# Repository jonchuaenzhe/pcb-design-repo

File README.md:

2020 May - Present
# PCB Design Archives

This repository is an archive of past completed PCB Designs on EAGLE and Altium for various projects.

## Altium

For the Altium Projects, the Schematics can be viewed by accessing the "Project Outputs" folder within each project and opening the schematic PDF file.

## EAGLE

For the EAGLE Projects, the Schematics and Layouts can be viewed directly in each project folder as a PDF file.

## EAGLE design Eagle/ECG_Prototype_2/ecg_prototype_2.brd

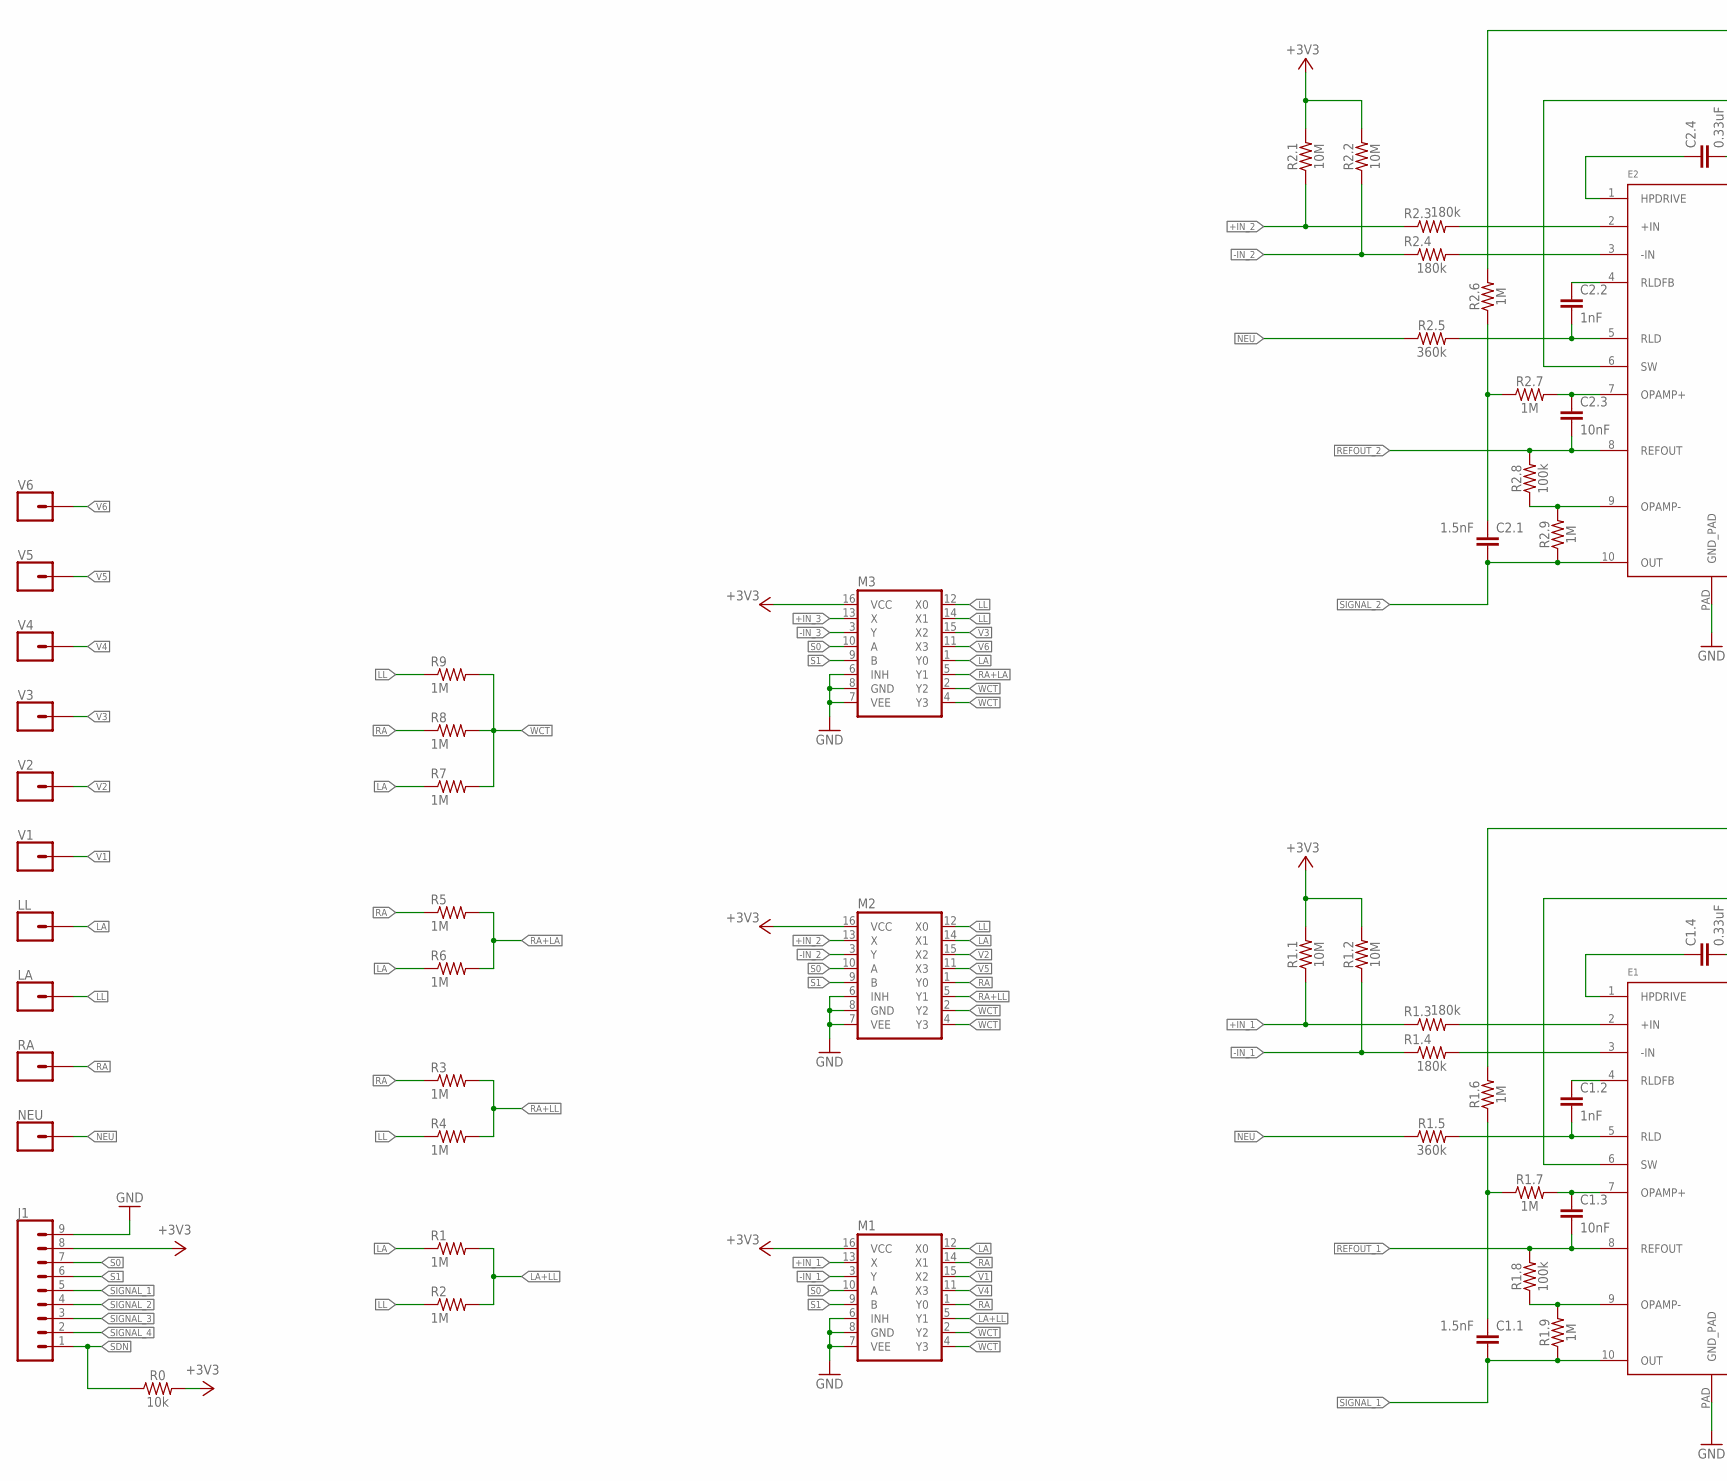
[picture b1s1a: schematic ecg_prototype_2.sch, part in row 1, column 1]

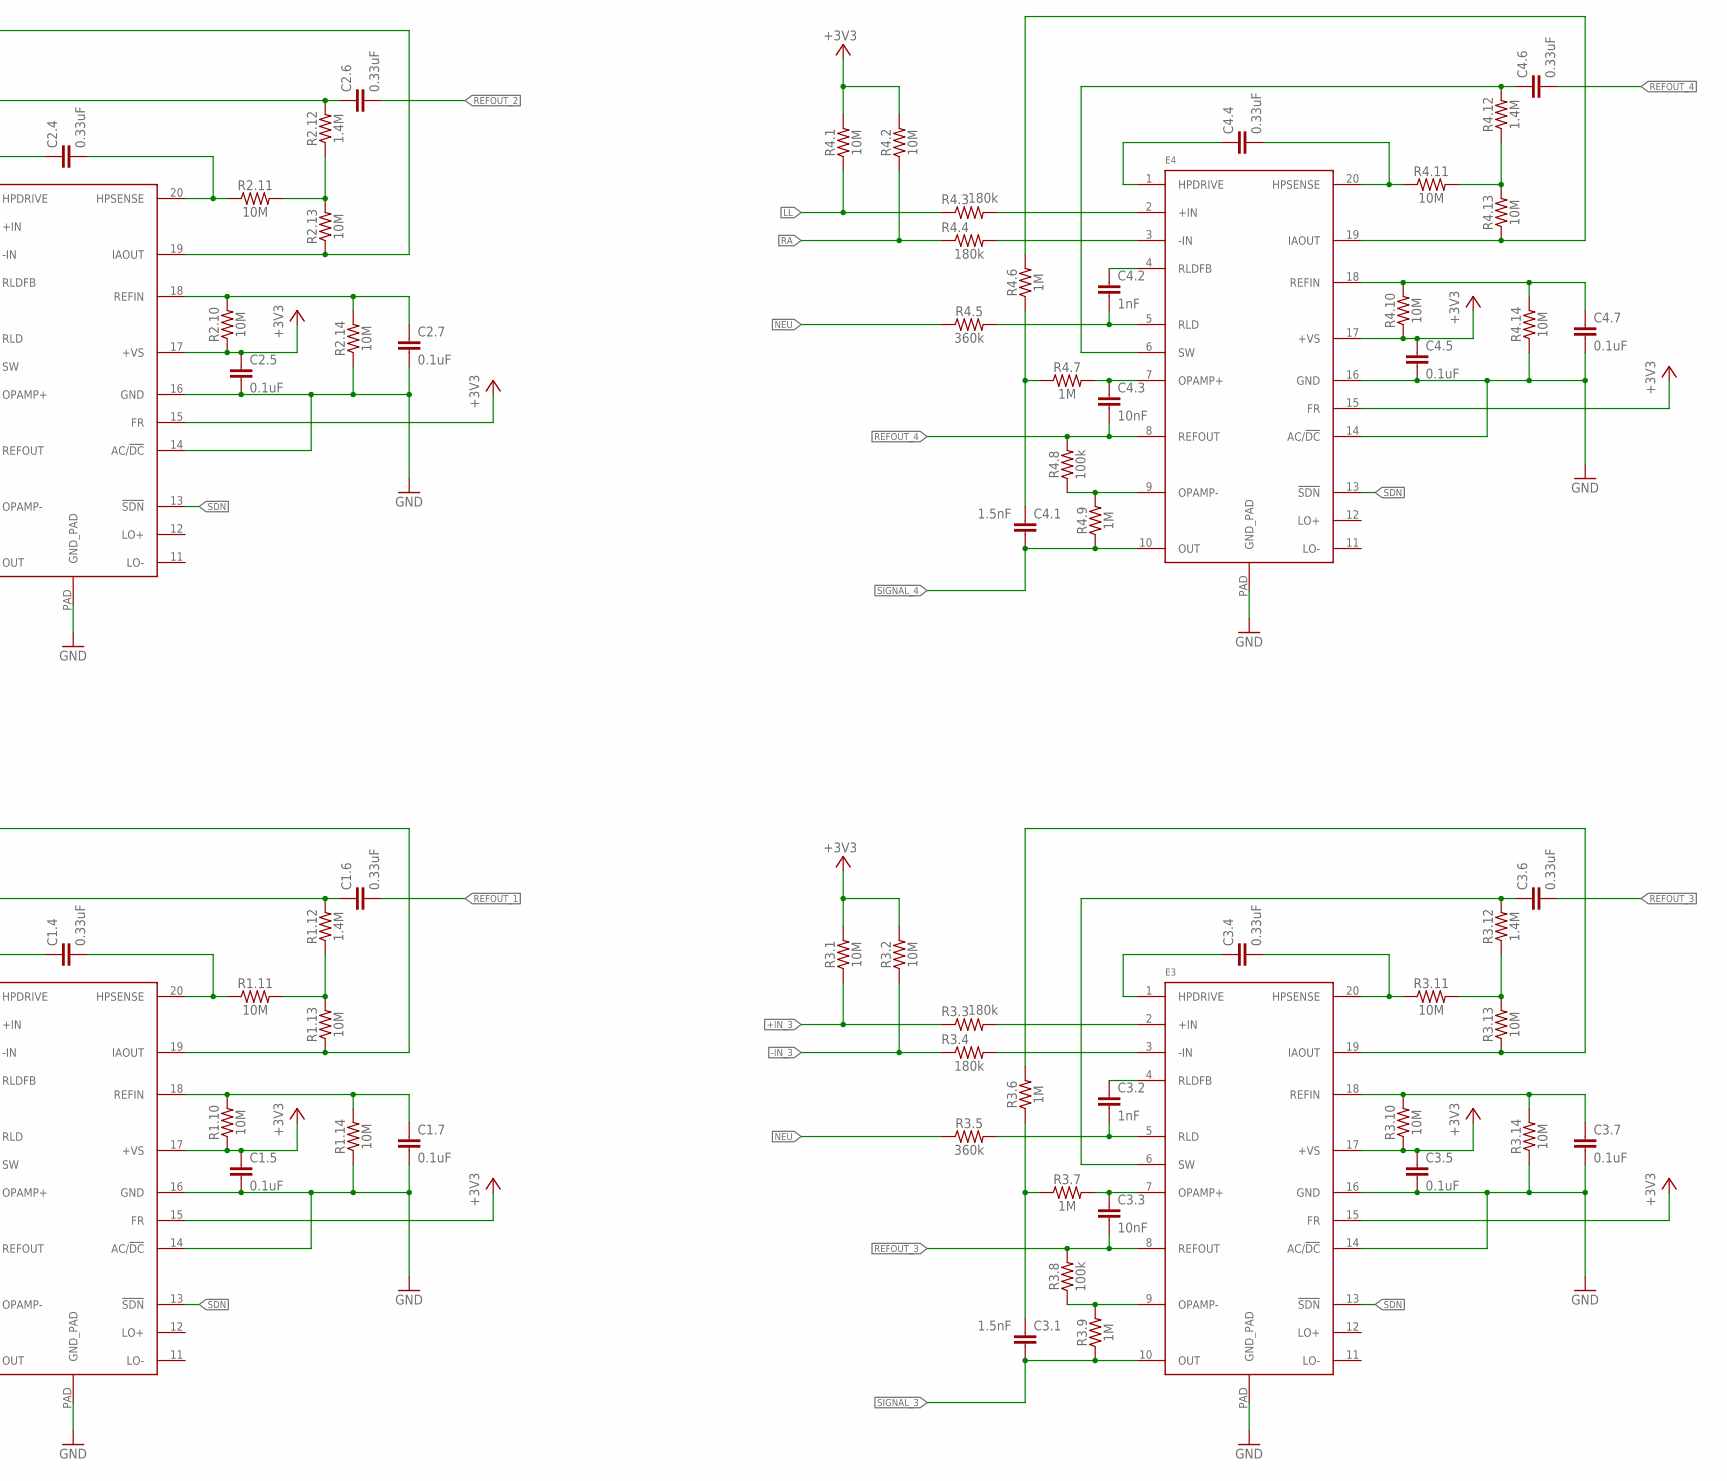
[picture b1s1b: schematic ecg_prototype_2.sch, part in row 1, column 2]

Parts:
C1.1, C2.1, C3.1, C4.1: 1.5nF; 0603-CAP
C1.2, C2.2, C3.2, C4.2: 1nF; 0603-CAP
C1.3, C2.3, C3.3, C4.3: 10nF; 0603-CAP
C1.4, C1.6, C2.4, C2.6, C3.4, C3.6, C4.4, C4.6: 0.33uF; 0805
C1.5, C1.7, C2.5, C2.7, C3.5, C3.7, C4.5, C4.7: 0.1uF; 0603-CAP
E1, E2, E3, E4: AD8232ACPZ-R7; LFCSP_20
J1: CONN_09; 1X09
LA: CONN_01; 1X01
LL: CONN_01; 1X01
M1, M2, M3: 74HC4052D; SO16
NEU: CONN_01; 1X01
R0: 10k; 0603
R1, R2, R3, R4, R5, R6, R7, R8, R9: 1M; 0402-RES
R1.1, R1.2, R1.10, R1.11, R1.13, R1.14, R2.1, R2.2, R2.10, R2.11, R2.13, R2.14, R3.1, R3.2, R3.10, R3.11, R3.13, R3.14, R4.1, R4.2, R4.10, R4.11, R4.13, R4.14: 10M; 0603
R1.3, R1.4, R2.3, R2.4, R3.3, R3.4, R4.3, R4.4: 180k; 0603
R1.5, R2.5, R3.5, R4.5: 360k; 0603
R1.6, R1.7, R1.9, R2.6, R2.7, R2.9, R3.6, R3.7, R3.9, R4.6, R4.7, R4.9: 1M; 0603
R1.8, R2.8, R3.8, R4.8: 100k; 0603
R1.12, R2.12, R3.12, R4.12: 1.4M; 0603
RA: CONN_01; 1X01
V1, V2, V3, V4, V5, V6: CONN_01; 1X01

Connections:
+3V3: C1.5.1, C2.5.1, C3.5.1, C4.5.1, E1.15 (FR), E1.17 (+VS), E2.15 (FR), E2.17 (+VS), E3.15 (FR), E3.17 (+VS), E4.15 (FR), E4.17 (+VS), J1.8, M1.16 (VCC), M2.16 (VCC), M3.16 (VCC), R0.2, R1.1.2, R1.2.2, R1.10.1, R2.1.2, R2.2.2, R2.10.1, R3.1.2, R3.2.2, R3.10.1, R4.1.2, R4.2.2, R4.10.1
+IN_1: M1.13 (X), R1.1.1, R1.3.1
+IN_2: M2.13 (X), R2.1.1, R2.3.1
+IN_3: M3.13 (X), R3.1.1, R3.3.1
-IN_1: M1.3 (Y), R1.2.1, R1.4.1
-IN_2: M2.3 (Y), R2.2.1, R2.4.1
-IN_3: M3.3 (Y), R3.2.1, R3.4.1
GND: C1.5.2, C1.7.2, C2.5.2, C2.7.2, C3.5.2, C3.7.2, C4.5.2, C4.7.2, E1.14 (AC/!DC), E1.16 (GND), E1.PAD (GND_PAD), E2.14 (AC/!DC), E2.16 (GND), E2.PAD (GND_PAD), E3.14 (AC/!DC), E3.16 (GND), E3.PAD (GND_PAD), E4.14 (AC/!DC), E4.16 (GND), E4.PAD (GND_PAD), J1.9, M1.6 (INH), M1.7 (VEE), M1.8 (GND), M2.6 (INH), M2.7 (VEE), M2.8 (GND), M3.6 (INH), M3.7 (VEE), M3.8 (GND), R1.14.1, R2.14.1, R3.14.1, R4.14.1
LA: LL.1, M1.12 (X0), M2.14 (X1), M3.1 (Y0), R1.1, R6.1, R7.1
LA+LL: M1.5 (Y1), R1.2, R2.2
LL: LA.1, M2.12 (X0), M3.12 (X0), M3.14 (X1), R2.1, R4.1, R4.1.1, R4.3.1, R9.1
unnamed: E1.9 (OPAMP-), R1.8.1, R1.9.2
unnamed: E2.2 (+IN), R2.3.2
unnamed: E1.2 (+IN), R1.3.2
unnamed: E1.3 (-IN), R1.4.2
unnamed: E2.3 (-IN), R2.4.2
unnamed: C1.1.1, R1.6.1, R1.7.1
unnamed: C1.3.1, E1.7 (OPAMP+), R1.7.2
unnamed: C1.2.1, E1.4 (RLDFB)
unnamed: C1.2.2, E1.5 (RLD), R1.5.2
unnamed: E1.19 (IAOUT), R1.6.2, R1.13.1
unnamed: C1.6.1, E1.6 (SW), R1.12.2
unnamed: C1.7.1, E1.18 (REFIN), R1.10.2, R1.14.2
unnamed: R1.11.2, R1.12.1, R1.13.2
unnamed: C1.4.2, E1.20 (HPSENSE), R1.11.1
unnamed: C1.4.1, E1.1 (HPDRIVE)
unnamed: C2.2.1, E2.4 (RLDFB)
unnamed: C2.2.2, E2.5 (RLD), R2.5.2
unnamed: C2.1.1, R2.6.1, R2.7.1
unnamed: C2.3.1, E2.7 (OPAMP+), R2.7.2
unnamed: E2.9 (OPAMP-), R2.8.1, R2.9.2
unnamed: E2.19 (IAOUT), R2.6.2, R2.13.1
unnamed: C2.6.1, E2.6 (SW), R2.12.2
unnamed: R2.11.2, R2.12.1, R2.13.2
unnamed: C2.4.2, E2.20 (HPSENSE), R2.11.1
unnamed: C2.4.1, E2.1 (HPDRIVE)
unnamed: C2.7.1, E2.18 (REFIN), R2.10.2, R2.14.2
unnamed: E3.2 (+IN), R3.3.2
unnamed: E3.3 (-IN), R3.4.2
unnamed: C3.2.1, E3.4 (RLDFB)
unnamed: C3.2.2, E3.5 (RLD), R3.5.2
unnamed: C3.1.1, R3.6.1, R3.7.1
unnamed: C3.3.1, E3.7 (OPAMP+), R3.7.2
unnamed: E3.9 (OPAMP-), R3.8.1, R3.9.2
unnamed: E3.19 (IAOUT), R3.6.2, R3.13.1
unnamed: C3.6.1, E3.6 (SW), R3.12.2
unnamed: R3.11.2, R3.12.1, R3.13.2
unnamed: C3.4.2, E3.20 (HPSENSE), R3.11.1
unnamed: C3.4.1, E3.1 (HPDRIVE)
unnamed: C3.7.1, E3.18 (REFIN), R3.10.2, R3.14.2
unnamed: E4.2 (+IN), R4.3.2
unnamed: E4.3 (-IN), R4.4.2
unnamed: C4.2.1, E4.4 (RLDFB)
unnamed: C4.2.2, E4.5 (RLD), R4.5.2
unnamed: C4.1.1, R4.6.1, R4.7.1
unnamed: C4.3.1, E4.7 (OPAMP+), R4.7.2
unnamed: E4.9 (OPAMP-), R4.8.1, R4.9.2
unnamed: E4.19 (IAOUT), R4.6.2, R4.13.1
unnamed: C4.6.1, E4.6 (SW), R4.12.2
unnamed: R4.11.2, R4.12.1, R4.13.2
unnamed: C4.4.2, E4.20 (HPSENSE), R4.11.1
unnamed: C4.4.1, E4.1 (HPDRIVE)
unnamed: C4.7.1, E4.18 (REFIN), R4.10.2, R4.14.2
NEU: NEU.1, R1.5.1, R2.5.1, R3.5.1, R4.5.1
RA: M1.1 (Y0), M1.14 (X1), M2.1 (Y0), R3.1, R4.2.1, R4.4.1, R5.1, R8.1, RA.1
RA+LA: M3.5 (Y1), R5.2, R6.2
RA+LL: M2.5 (Y1), R3.2, R4.2
REFOUT_1: C1.3.2, C1.6.2, E1.8 (REFOUT), R1.8.2
REFOUT_2: C2.3.2, C2.6.2, E2.8 (REFOUT), R2.8.2
REFOUT_3: C3.3.2, C3.6.2, E3.8 (REFOUT), R3.8.2
REFOUT_4: C4.3.2, C4.6.2, E4.8 (REFOUT), R4.8.2
S0: J1.7, M1.10 (A), M2.10 (A), M3.10 (A)
S1: J1.6, M1.9 (B), M2.9 (B), M3.9 (B)
SDN: E1.13 (!SDN), E2.13 (!SDN), E3.13 (!SDN), E4.13 (!SDN), J1.1, R0.1
SIGNAL_1: C1.1.2, E1.10 (OUT), J1.5, R1.9.1
SIGNAL_2: C2.1.2, E2.10 (OUT), J1.4, R2.9.1
SIGNAL_3: C3.1.2, E3.10 (OUT), J1.3, R3.9.1
SIGNAL_4: C4.1.2, E4.10 (OUT), J1.2, R4.9.1
V1: M1.15 (X2), V1.1
V2: M2.15 (X2), V2.1
V3: M3.15 (X2), V3.1
V4: M1.11 (X3), V4.1
V5: M2.11 (X3), V5.1
V6: M3.11 (X3), V6.1
WCT: M1.2 (Y2), M1.4 (Y3), M2.2 (Y2), M2.4 (Y3), M3.2 (Y2), M3.4 (Y3), R7.2, R8.2, R9.2

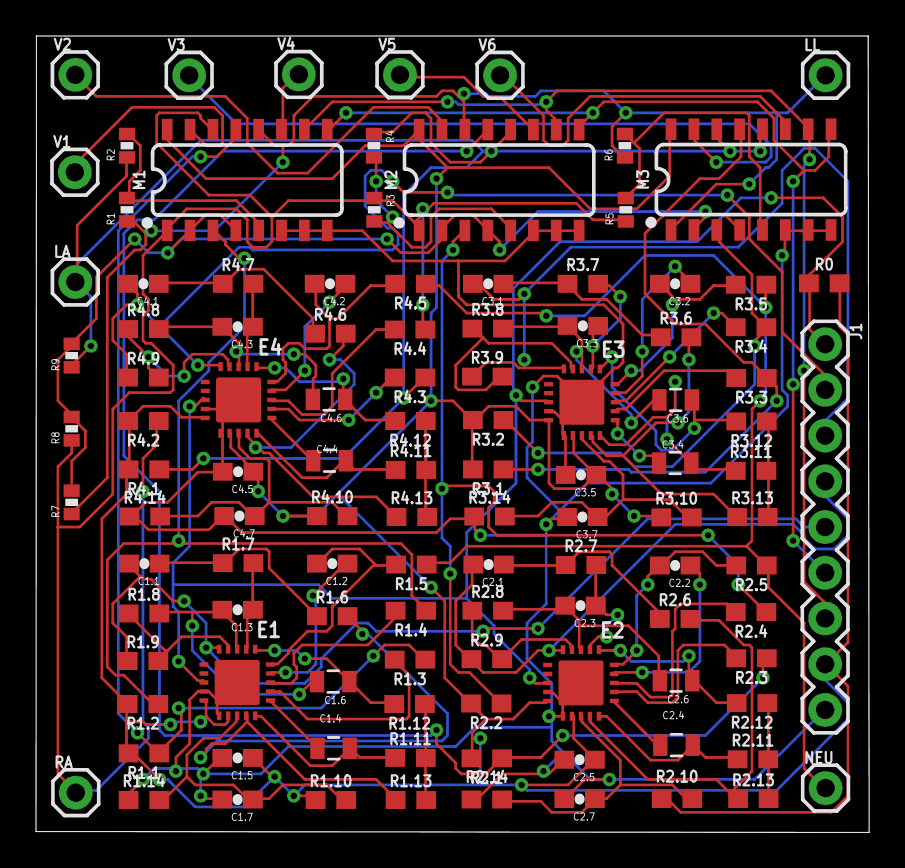
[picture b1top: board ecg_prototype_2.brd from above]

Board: 2 copper layers, 46.3 x 44.2 mm, 112 parts (0 on the bottom side), 85 nets.

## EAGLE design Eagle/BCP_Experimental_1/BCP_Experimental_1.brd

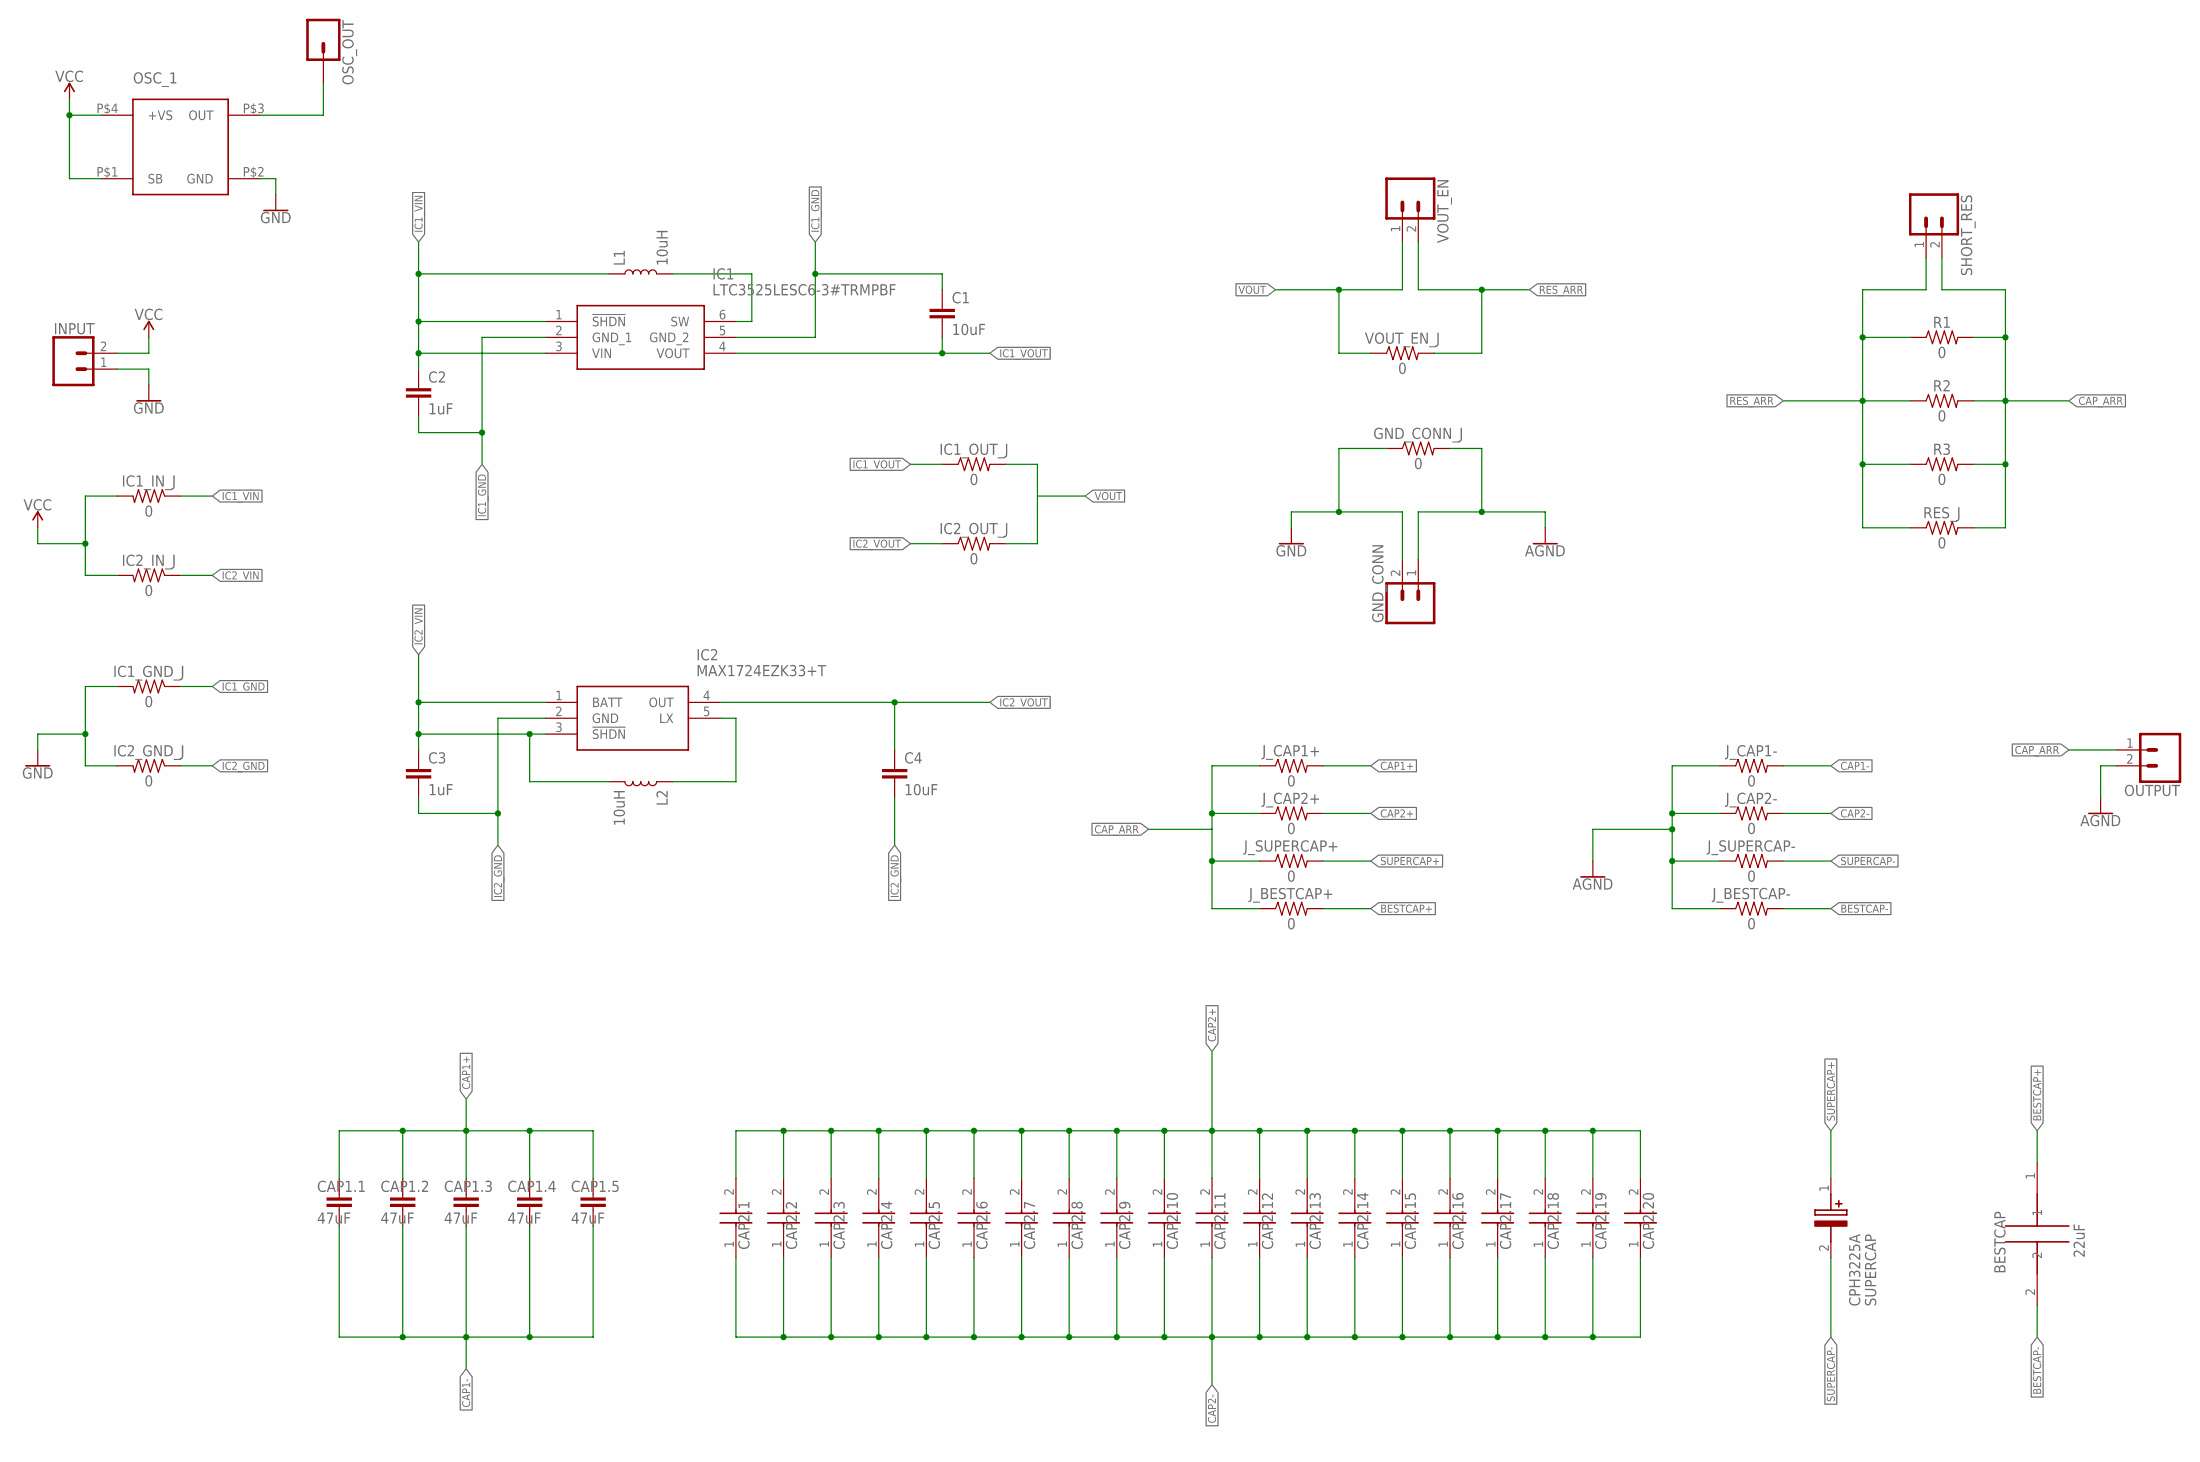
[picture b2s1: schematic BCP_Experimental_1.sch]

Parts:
BESTCAP: BZ054B223ZNB
C1, C4: 10uF; 0603
C2, C3: 1uF; 0603
CAP1.1, CAP1.2, CAP1.3, CAP1.4, CAP1.5: 47uF; 1206
CAP2.1, CAP2.2, CAP2.3, CAP2.4, CAP2.5, CAP2.6, CAP2.7, CAP2.8, CAP2.9, CAP2.10, CAP2.11, CAP2.12, CAP2.13, CAP2.14, CAP2.15, CAP2.16, CAP2.17, CAP2.18, CAP2.19, CAP2.20: AMK432BJ477MM-T; CAPC4532X270N
GND_CONN: CONN_02; 1X02
GND_CONN_J: 0; 0402
IC1: LTC3525LESC6-3#TRMPBF; SOT65P210X100-6N
IC1_GND_J, IC1_IN_J, IC1_OUT_J, IC2_GND_J, IC2_IN_J, IC2_OUT_J: 0; 0402
IC2: MAX1724EZK33+T; SOT95P275X110-5N
INPUT: CONN_02; 1X02
J_BESTCAP+: 0; 0402
J_BESTCAP-: 0; 0402
J_CAP1+, J_CAP1-, J_CAP2+, J_CAP2-: 0; 0402
J_SUPERCAP+: 0; 0402
J_SUPERCAP-: 0; 0402
L1, L2: 10uH; 0603
OSC_1: 830202536501
OSC_OUT: CONN_01; 1X01
OUTPUT: CONN_02; 1X02
R1, R2, R3: 0; 0603
RES_J: 0; 0402
SHORT_RES: CONN_02; 1X02
SUPERCAP: CPH3225A
VOUT_EN: CONN_02; 1X02
VOUT_EN_J: 0; 0402

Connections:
AGND: GND_CONN.1, GND_CONN_J.2, J_BESTCAP-.1, J_CAP1-.1, J_CAP2-.1, J_SUPERCAP-.1, OUTPUT.2
BESTCAP+: BESTCAP.1, J_BESTCAP+.2
BESTCAP-: BESTCAP.2, J_BESTCAP-.2
CAP1+: CAP1.1.1, CAP1.2.1, CAP1.3.1, CAP1.4.1, CAP1.5.1, J_CAP1+.2
CAP1-: CAP1.1.2, CAP1.2.2, CAP1.3.2, CAP1.4.2, CAP1.5.2, J_CAP1-.2
CAP2+: CAP2.1.2, CAP2.2.2, CAP2.3.2, CAP2.4.2, CAP2.5.2, CAP2.6.2, CAP2.7.2, CAP2.8.2, CAP2.9.2, CAP2.10.2, CAP2.11.2, CAP2.12.2, CAP2.13.2, CAP2.14.2, CAP2.15.2, CAP2.16.2, CAP2.17.2, CAP2.18.2, CAP2.19.2, CAP2.20.2, J_CAP2+.2
CAP2-: CAP2.1.1, CAP2.2.1, CAP2.3.1, CAP2.4.1, CAP2.5.1, CAP2.6.1, CAP2.7.1, CAP2.8.1, CAP2.9.1, CAP2.10.1, CAP2.11.1, CAP2.12.1, CAP2.13.1, CAP2.14.1, CAP2.15.1, CAP2.16.1, CAP2.17.1, CAP2.18.1, CAP2.19.1, CAP2.20.1, J_CAP2-.2
CAP_ARR: J_BESTCAP+.1, J_CAP1+.1, J_CAP2+.1, J_SUPERCAP+.1, OUTPUT.1, R1.2, R2.2, R3.2, RES_J.2, SHORT_RES.2
GND: GND_CONN.2, GND_CONN_J.1, IC1_GND_J.2, IC2_GND_J.2, INPUT.1, OSC_1.P$2 (GND)
IC1_GND: C1.1, C2.2, IC1.2 (GND_1), IC1.5 (GND_2), IC1_GND_J.1
IC1_VIN: C2.1, IC1.1 (!SHDN), IC1.3 (VIN), IC1_IN_J.1, L1.1
IC1_VOUT: C1.2, IC1.4 (VOUT), IC1_OUT_J.1
IC2_GND: C3.2, C4.2, IC2.2 (GND), IC2_GND_J.1
IC2_VIN: C3.1, IC2.1 (BATT), IC2.3 (!SHDN), IC2_IN_J.1, L2.2
IC2_VOUT: C4.1, IC2.4 (OUT), IC2_OUT_J.1
unnamed: IC1.6 (SW), L1.2
unnamed: IC2.5 (LX), L2.1
unnamed: OSC_1.P$3 (OUT), OSC_OUT.1
RES_ARR: R1.1, R2.1, R3.1, RES_J.1, SHORT_RES.1, VOUT_EN.2, VOUT_EN_J.2
SUPERCAP+: J_SUPERCAP+.2, SUPERCAP.1 (+)
SUPERCAP-: J_SUPERCAP-.2, SUPERCAP.2 (-)
VCC: IC1_IN_J.2, IC2_IN_J.2, INPUT.2, OSC_1.P$1 (SB), OSC_1.P$4 (+VS)
VOUT: IC1_OUT_J.2, IC2_OUT_J.2, VOUT_EN.1, VOUT_EN_J.1

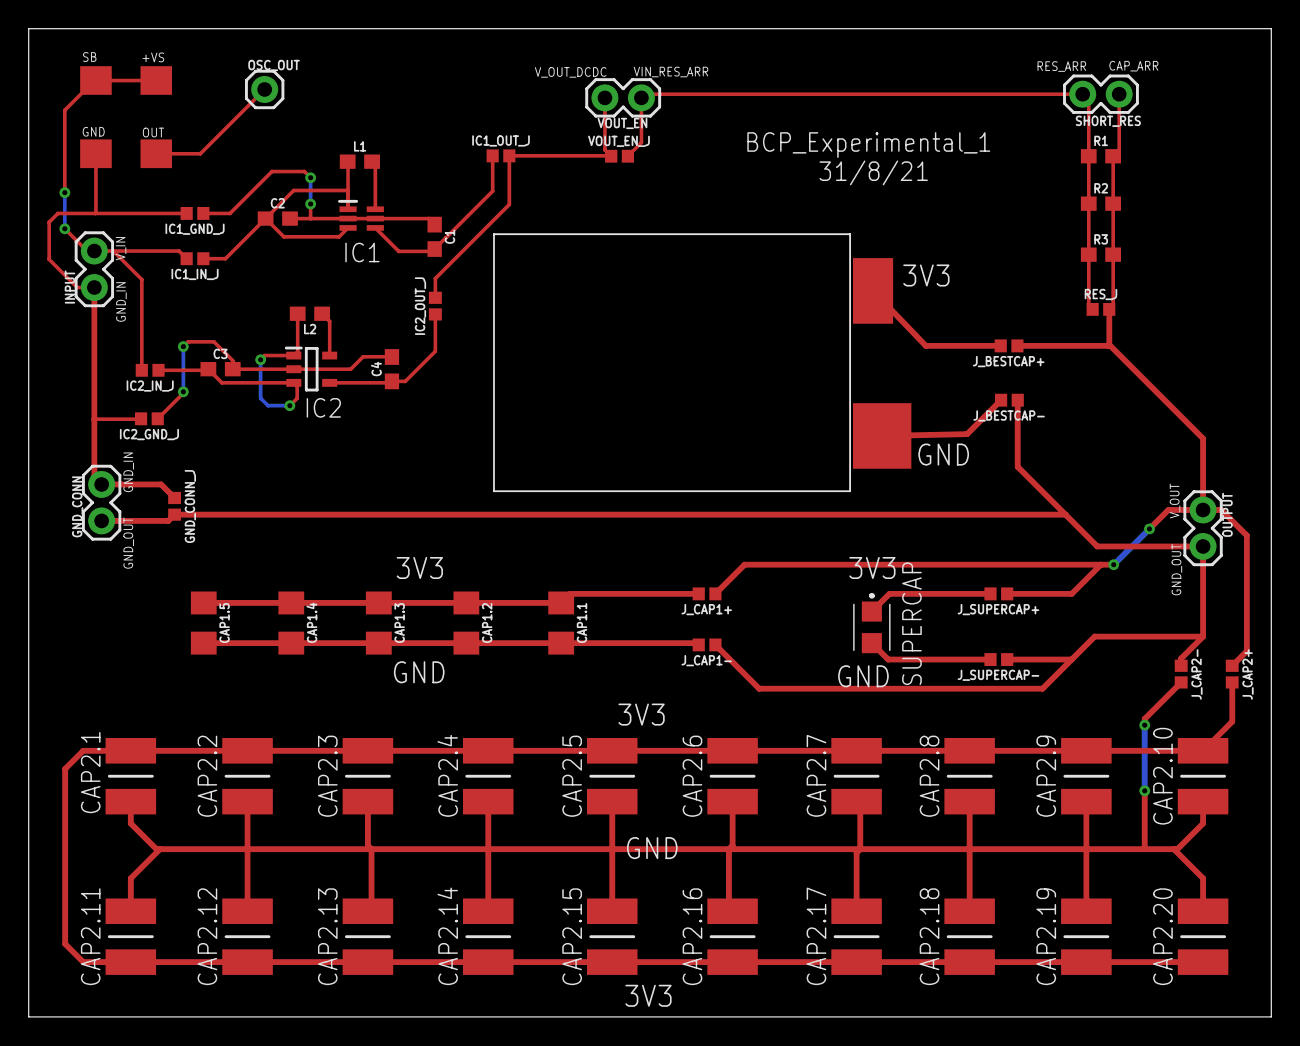
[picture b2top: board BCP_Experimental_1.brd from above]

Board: 2 copper layers, 86.5 x 68.8 mm, 62 parts (0 on the bottom side), 23 nets.

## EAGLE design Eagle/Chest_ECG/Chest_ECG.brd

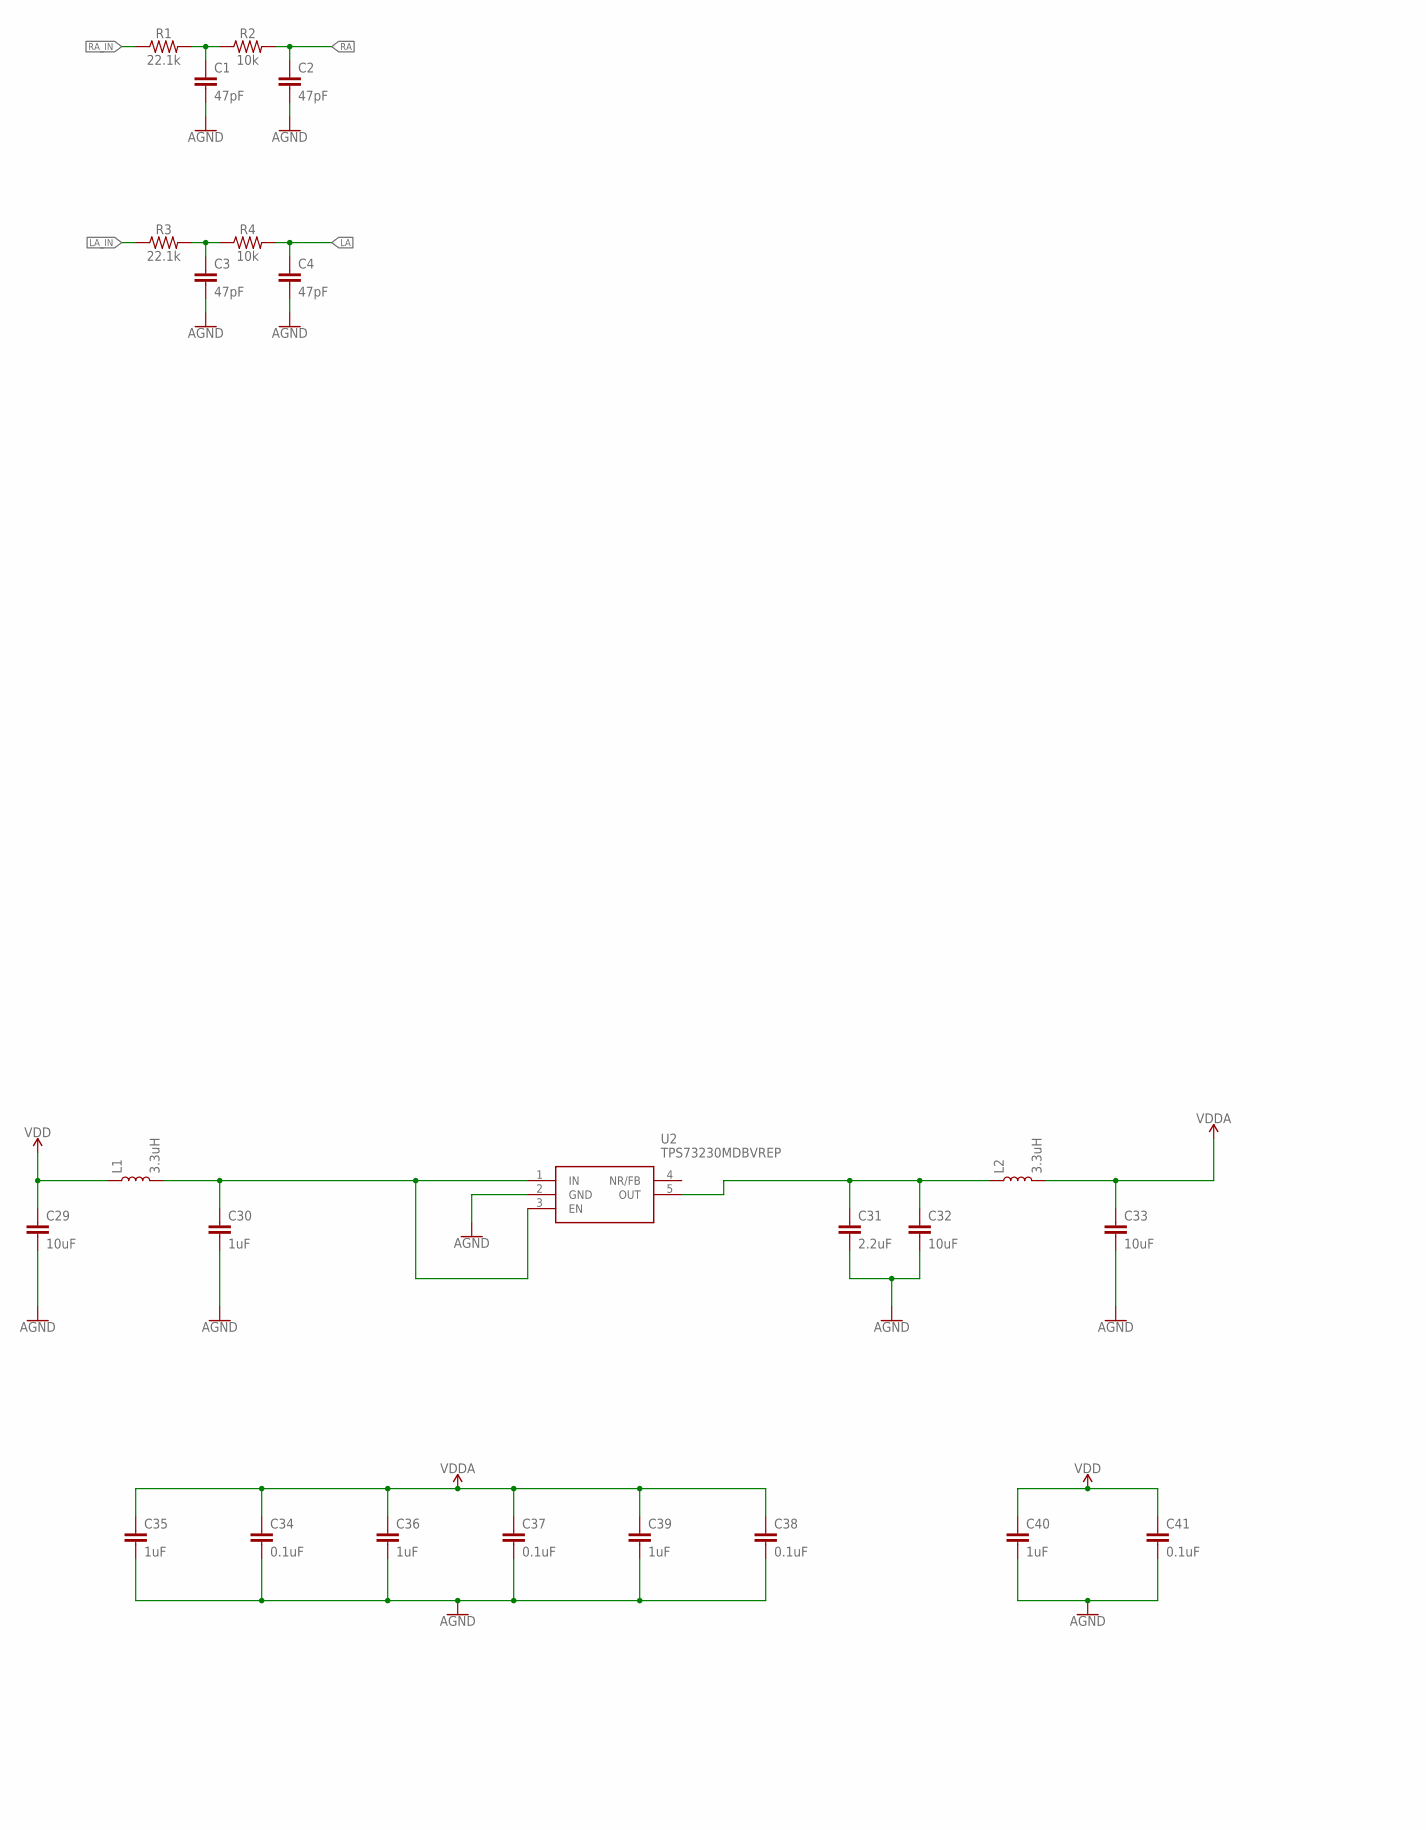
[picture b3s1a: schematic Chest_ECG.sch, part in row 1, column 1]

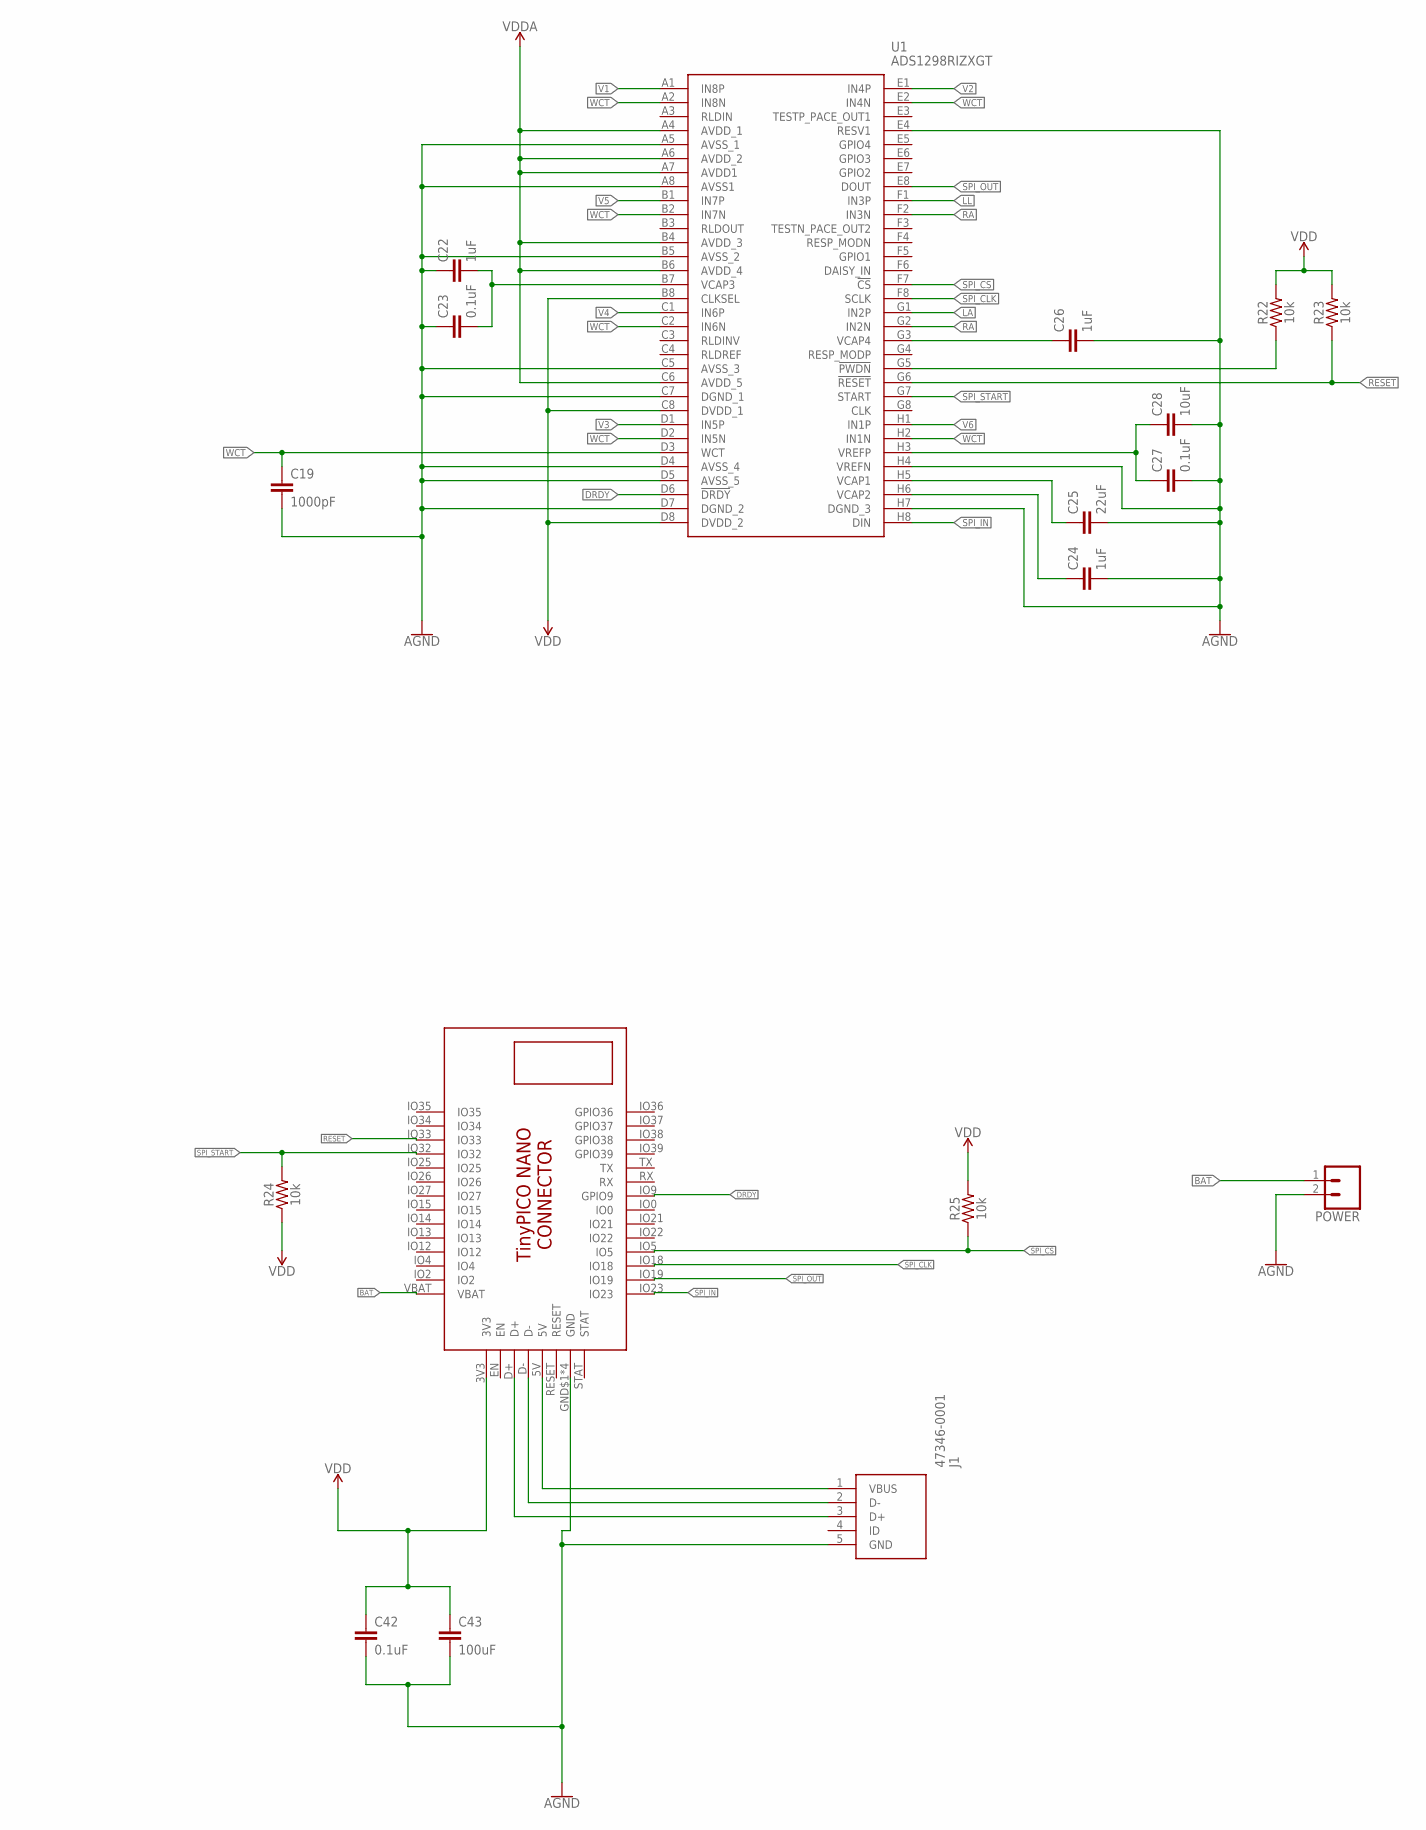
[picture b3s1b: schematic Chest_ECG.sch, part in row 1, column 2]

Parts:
C1, C2, C3, C4: 47pF; 0603
C19: 1000pF; 0603
C22, C24, C26, C30, C35, C36, C39, C40: 1uF; 0603
C23, C27, C34, C37, C38, C41, C42: 0.1uF; 0603
C25: 22uF; 0805
C28, C29, C32, C33: 10uF; 0805
C31: 2.2uF; 0603
C43: 100uF; 0805
J1: 47346-0001
L1, L2: 3.3uH; 0805
POWER: CONN_02; 1X02
R1, R3: 22.1k; 0603
R2, R4, R22, R23, R24, R25: 10k; 0603
U1: ADS1298RIZXGT; BGA64C80P8X8_800X800X145
U2: TPS73230MDBVREP; SOT95P280X145-5N
U3: TINYPICO-NANO-CONNECTOR

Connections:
AGND: C1.2, C2.2, C3.2, C4.2, C19.2, C22.1, C23.1, C24.2, C25.2, C26.2, C27.2, C28.2, C29.2, C30.2, C31.2, C32.2, C33.2, C34.2, C35.2, C36.2, C37.2, C38.2, C39.2, C40.2, C41.2, C42.2, C43.2, J1.5 (GND), POWER.2, U1.A5 (AVSS_1), U1.A8 (AVSS1), U1.B5 (AVSS_2), U1.C5 (AVSS_3), U1.C7 (DGND_1), U1.D4 (AVSS_4), U1.D5 (AVSS_5), U1.D7 (DGND_2), U1.E4 (RESV1), U1.H4 (VREFN), U1.H7 (DGND_3), U2.2 (GND), U3.GND$1 (GND), U3.GND$2 (GND), U3.GND$3 (GND), U3.GND$4 (GND)
BAT: POWER.1, U3.VBAT
DRDY: U1.D6 (!DRDY), U3.IO9 (GPIO9)
LA: C4.1, R4.2, U1.G1 (IN2P)
LA_IN: R3.1
LL: U1.F1 (IN3P)
unnamed: C1.1, R1.2, R2.1
unnamed: C3.1, R3.2, R4.1
unnamed: C22.2, C23.2, U1.B7 (VCAP3)
unnamed: R22.1, U1.G5 (!PWDN)
unnamed: C24.1, U1.H6 (VCAP2)
unnamed: C27.1, C28.1, U1.H3 (VREFP)
unnamed: C25.1, U1.H5 (VCAP1)
unnamed: C26.1, U1.G3 (VCAP4)
unnamed: C31.1, C32.1, L2.1, U2.5 (OUT)
unnamed: J1.3 (D+), U3.D+
unnamed: J1.2 (D-), U3.D-
unnamed: J1.1 (VBUS), U3.5V
unnamed: C30.1, L1.2, U2.1 (IN), U2.3 (EN)
RA: C2.1, R2.2, U1.F2 (IN3N), U1.G2 (IN2N)
RA_IN: R1.1
RESET: R23.1, U1.G6 (!RESET), U3.IO33
SPI_CLK: U1.F8 (SCLK), U3.IO18
SPI_CS: R25.1, U1.F7 (!CS), U3.IO5
SPI_IN: U1.H8 (DIN), U3.IO23
SPI_OUT: U1.E8 (DOUT), U3.IO19
SPI_START: R24.2, U1.G7 (START), U3.IO32
V1: U1.A1 (IN8P)
V2: U1.E1 (IN4P)
V3: U1.D1 (IN5P)
V4: U1.C1 (IN6P)
V5: U1.B1 (IN7P)
V6: U1.H1 (IN1P)
VDD: C29.1, C40.1, C41.1, C42.1, C43.1, L1.1, R22.2, R23.2, R24.1, R25.2, U1.B8 (CLKSEL), U1.C8 (DVDD_1), U1.D8 (DVDD_2), U3.3V3
VDDA: C33.1, C34.1, C35.1, C36.1, C37.1, C38.1, C39.1, L2.2, U1.A4 (AVDD_1), U1.A6 (AVDD_2), U1.A7 (AVDD1), U1.B4 (AVDD_3), U1.B6 (AVDD_4), U1.C6 (AVDD_5)
WCT: C19.1, U1.A2 (IN8N), U1.B2 (IN7N), U1.C2 (IN6N), U1.D2 (IN5N), U1.D3 (WCT), U1.E2 (IN4N), U1.H2 (IN1N)

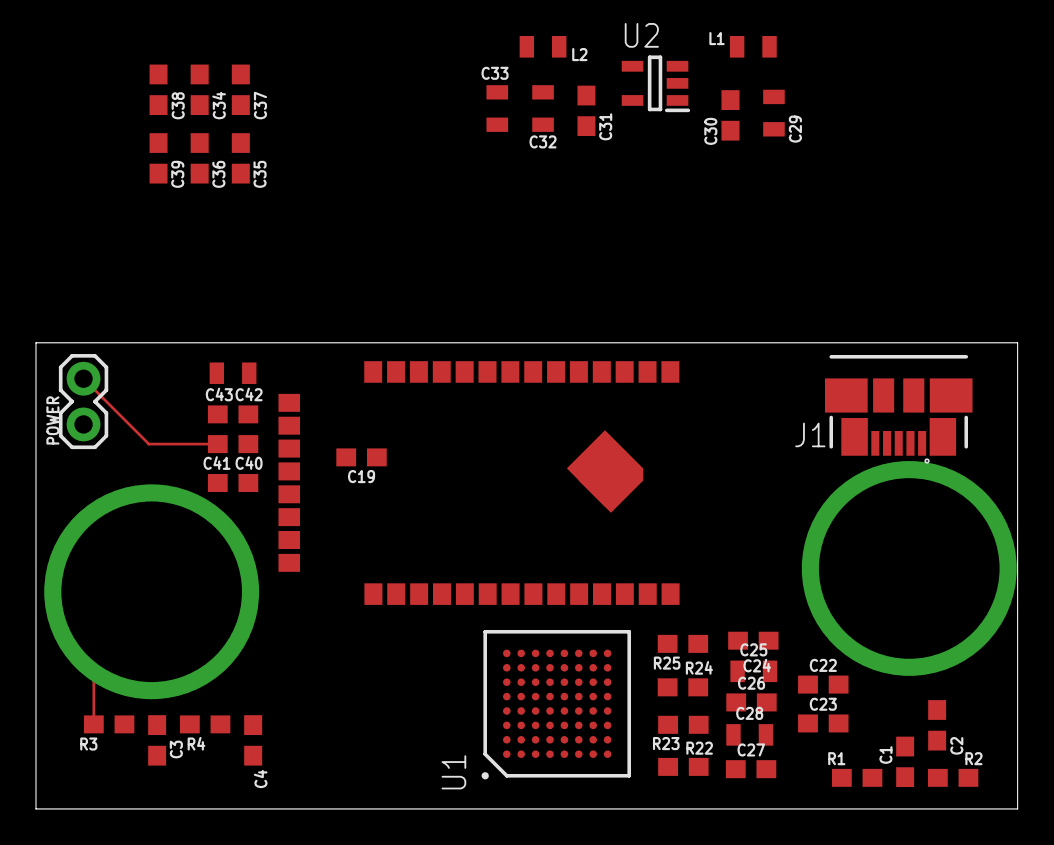
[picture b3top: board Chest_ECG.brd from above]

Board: 2 copper layers, 54.5 x 25.9 mm, 42 parts (0 on the bottom side), 27 nets.

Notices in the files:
parts and their libraries:
SparkFun-Capacitors: Licensing: Creative Commons ShareAlike 4.0 International - https://creativecommons.org/licenses/by-sa/4.0
SparkFun-Passives: Licensing: CC v3.0 Share-Alike You are welcome to use this library for commercial purposes.
